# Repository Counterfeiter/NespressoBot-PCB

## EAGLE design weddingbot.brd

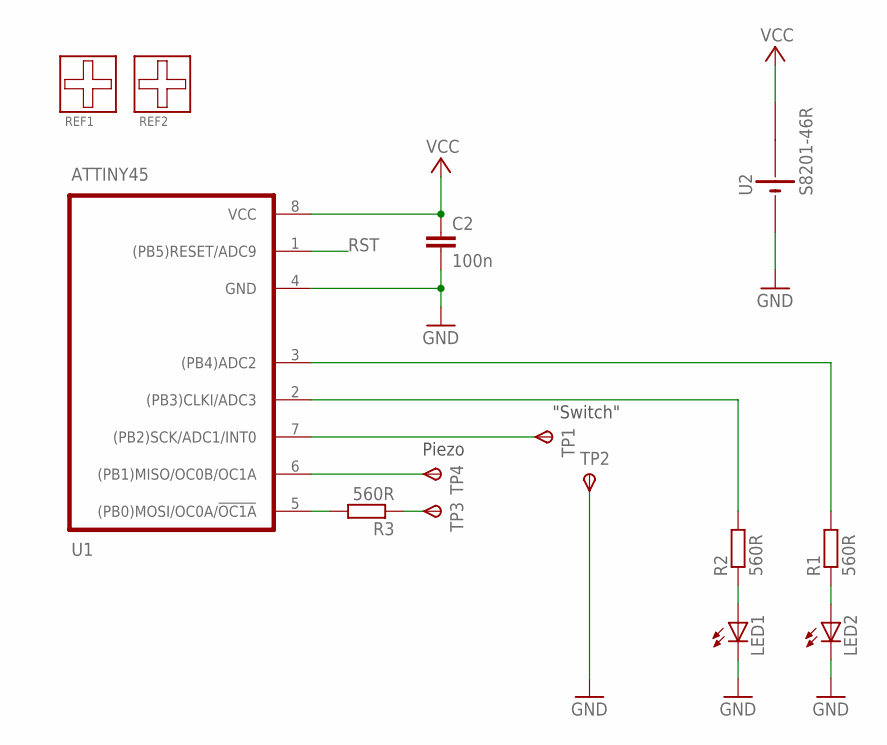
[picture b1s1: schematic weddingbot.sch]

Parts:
C2: 100n; C0603
LED1, LED2: LEDMEINE; CHIPLED_REV_1206
R1, R2, R3: 560R; R0603
REF1, REF2: FIDUCIAL_ROUND; REF_ROUND
TP1, TP2, TP3, TP4: TPSTP20R; TP20R
U1: ATTINY45; SOIC8
U2: S8201-46R

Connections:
GND: C2.2, LED1.C, LED2.C, TP2.TP, U1.4 (GND), U2.P1 (GND)
unnamed: R3.2, U1.5 ((PB0)MOSI/OC0A/!OC1A)
unnamed: LED2.A, R1.1
unnamed: LED1.A, R2.1
unnamed: TP1.TP, U1.7 ((PB2)SCK/ADC1/INT0)
unnamed: R3.1, TP3.TP
unnamed: TP4.TP, U1.6 ((PB1)MISO/OC0B/OC1A)
NET1: R2.2, U1.2 ((PB3)CLKI/ADC3)
RST: U1.1 ((PB5)RESET/ADC9)
SCK: R1.2, U1.3 ((PB4)ADC2)
VCC: C2.1, U1.8 (VCC), U2.P2 (VV1)

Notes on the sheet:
"Switch"
Piezo

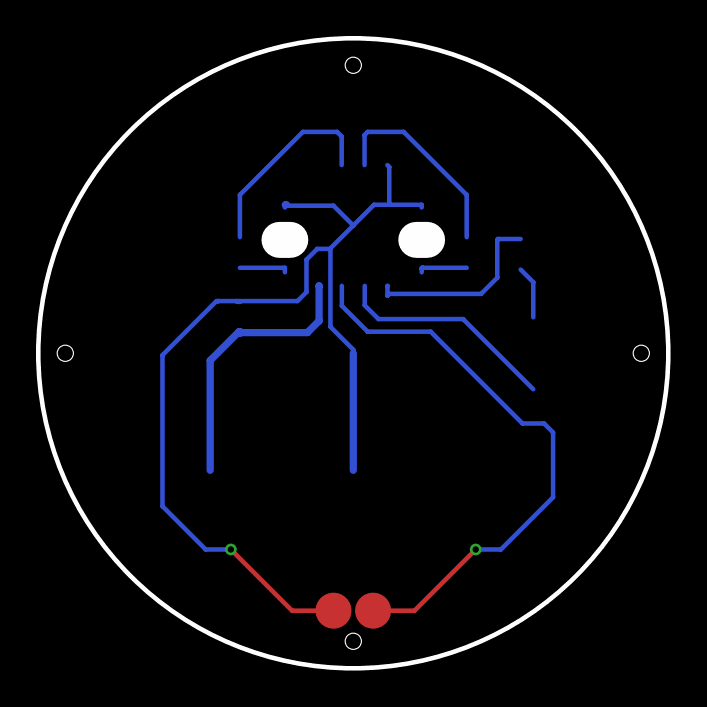
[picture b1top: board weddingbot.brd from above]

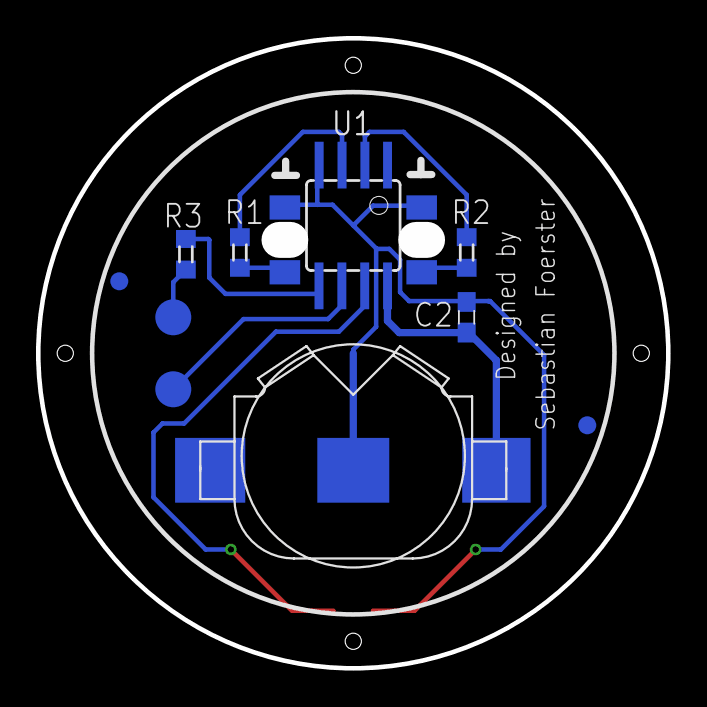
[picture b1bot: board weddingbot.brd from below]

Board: 2 copper layers, 33.3 x 33.3 mm, 14 parts (12 on the bottom side), 10 nets.

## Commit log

2018-04-13 - inital commit - optimized PCB for Nespresso/Wedding - Bot
